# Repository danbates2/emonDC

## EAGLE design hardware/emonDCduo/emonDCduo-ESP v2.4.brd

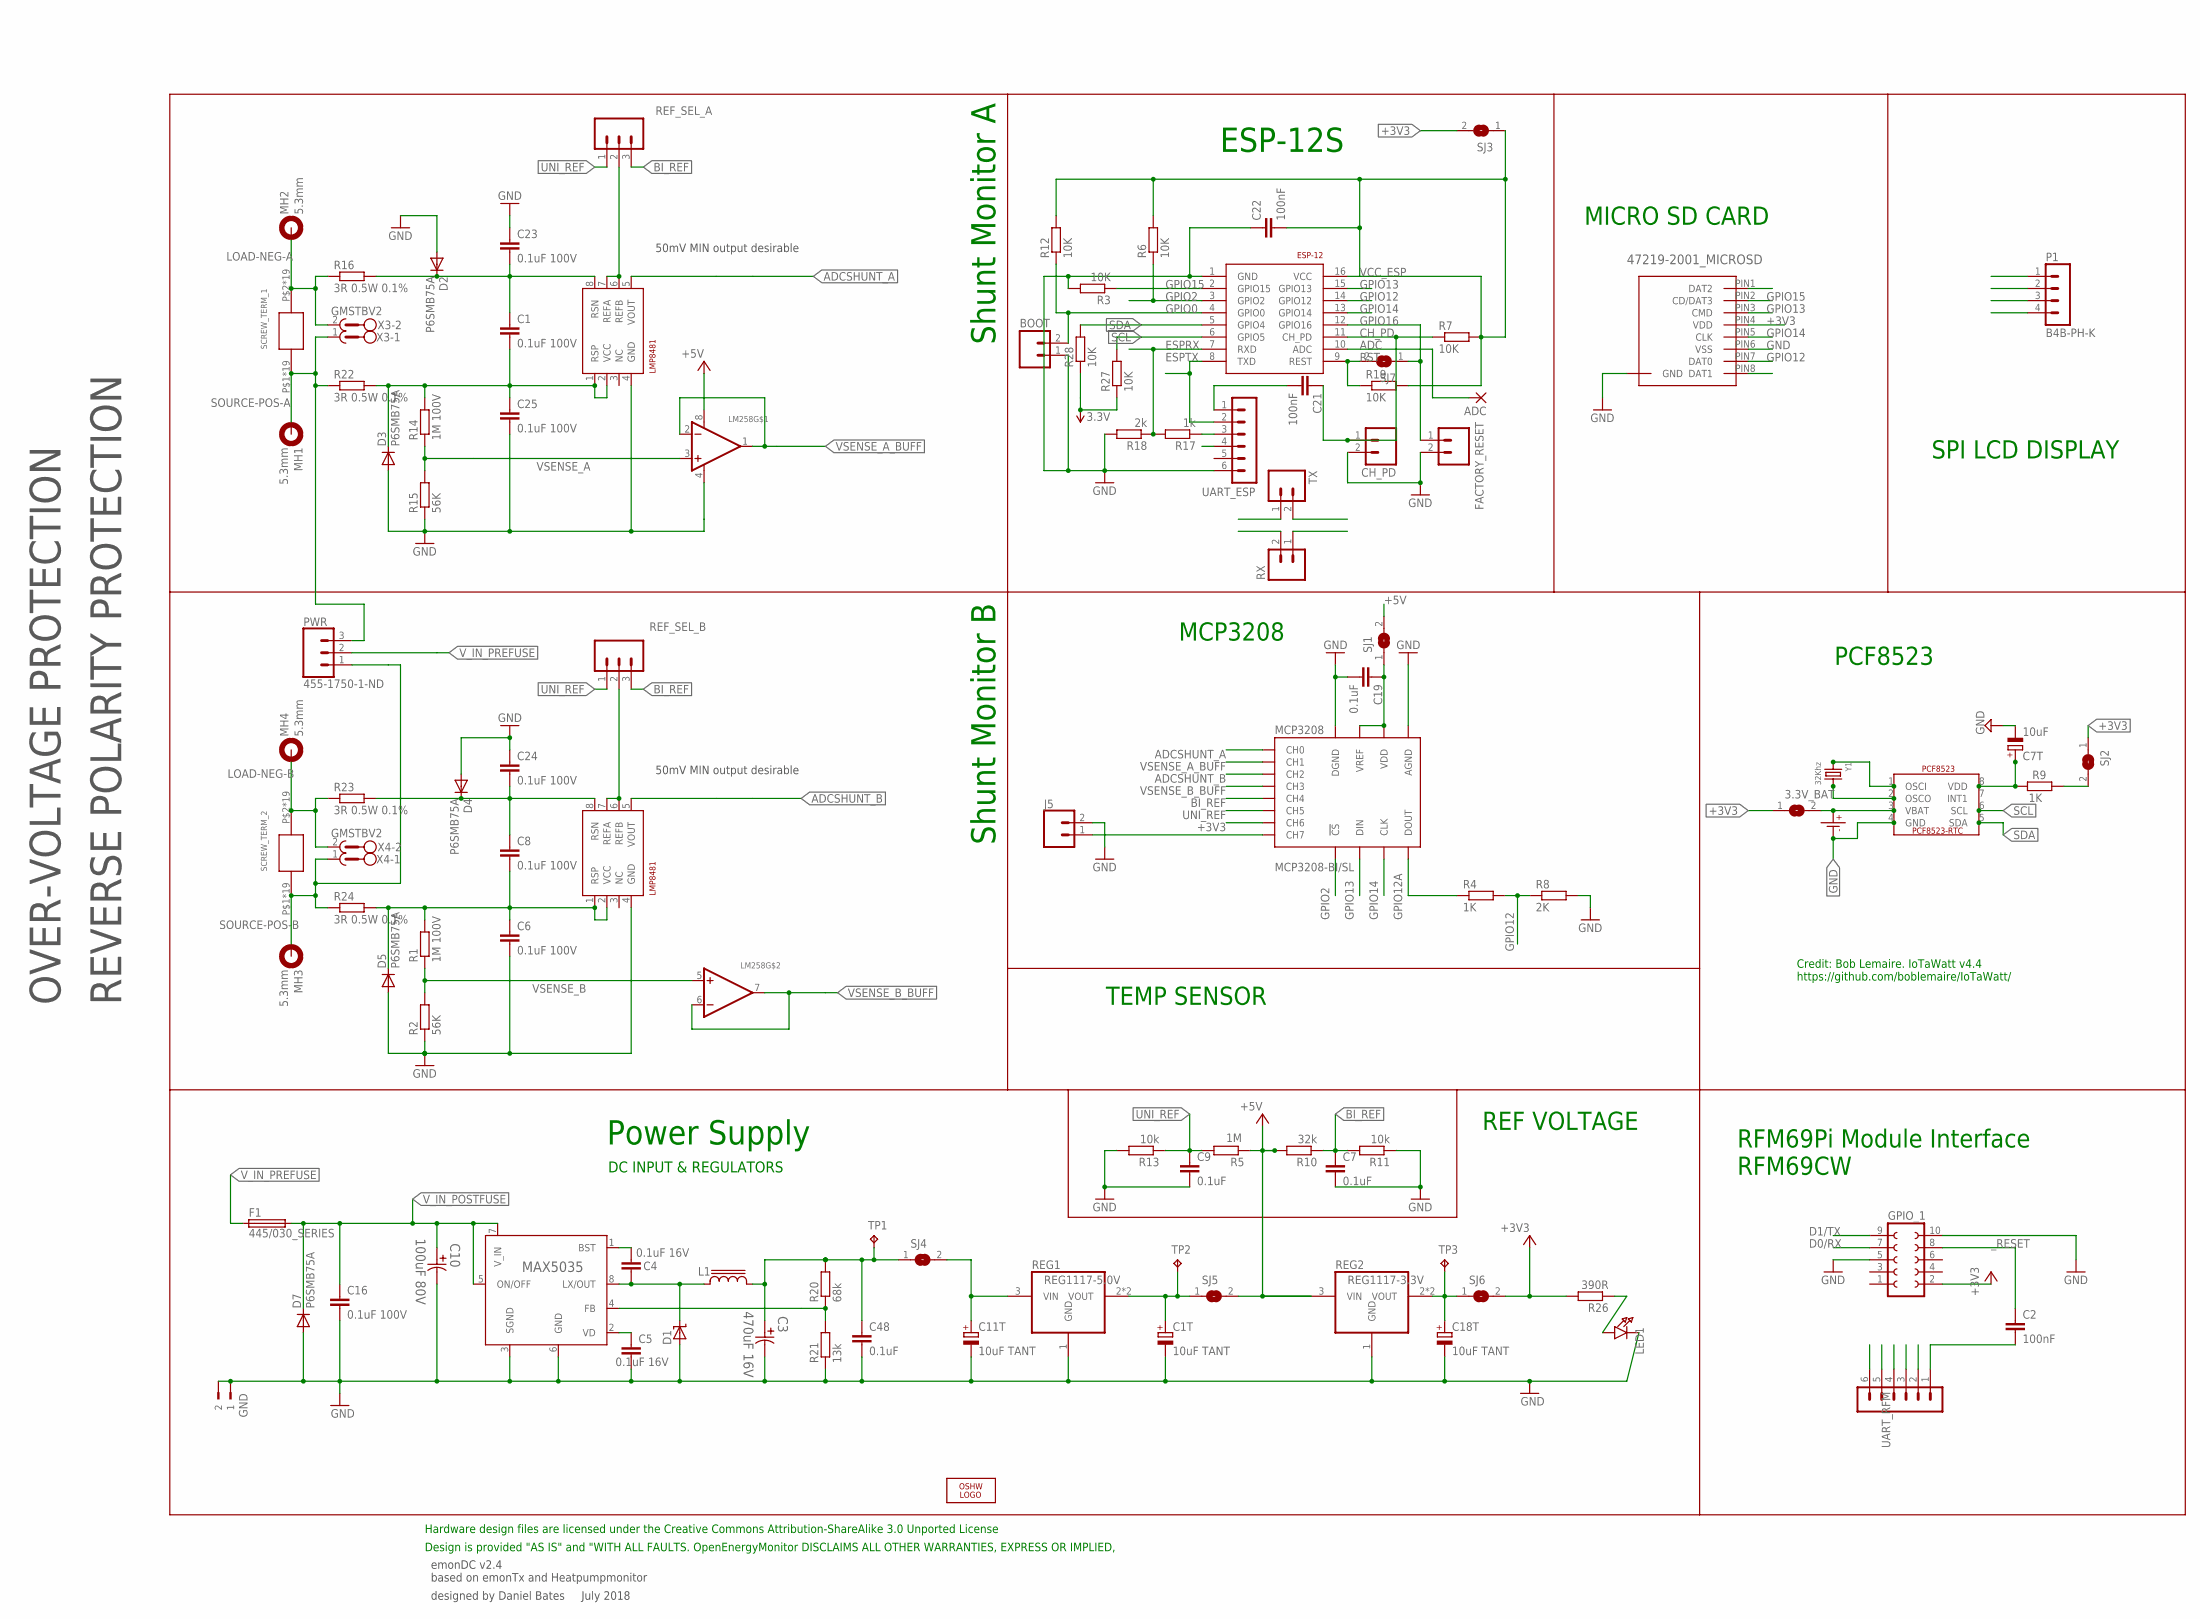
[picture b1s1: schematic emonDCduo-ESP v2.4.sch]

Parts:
3.3V_BAT: SJ-CONCON; SJ-CON
ADC: 2,15/1,0
BOOT: M02PTH; 1X02
C1, C6, C8, C23, C24, C25: 0.1uF 100V; C0603; MPN C1608X7S2A104K080AB
C1T, C11T, C18T: 10uF TANT; C0603POL
C2, C21, C22: 100nF; C0603
C3: 470uF 16V; CAPAE830X1050N
C4, C5: 0.1uF 16V; C0603
C7, C9, C19, C48: 0.1uF; C0603
C7T: 10uF; C0603POL
C10: 100uF 80V; CAPAE1350X1400N
C16: 0.1uF 100V; C0603
CH_PD: M02PTH; 1X02
CR1220: CR1220SMD; MPN Harwin S8411-45R
D1: MBRS1100T3G; SMB_1; MPN MBRS1100T3G
D2, D3, D4, D5, D7: P6SMB75A; DO214AA
ESP-12: ESP8266_ESP-12; ESP8266-ESP12
F1: 445/030_SERIES; 445/030_SERIES_LITTELFUSE
GND: 180-2
GPIO_1: FE05-2_RFM69PI_OUTLINERFM69PI; FE05-2_RFM69PI_OULTINE
IO16: FACTORY_RESET; 1X02
J5: CONN_02; 1X02
L1: SRR1208; SSR1208; MPN SRR1208-151YL
LED1: LED1206; CHIPLED_1206
LM258: LM358; SOIC8_150MIL
LOGO1: OSHW_LOGO_6MILX0200-NT; OSHW_6X200_NOTEXT
MCP3208: MCP3208-BI/SL; SOIC16
MH1, MH2, MH3, MH4: 5.3mm; 5,3//11-PAD
MICRO_SD: 47219-2001_MICROSD
P1: B4B-PH-K
PCF8523: PCF8523_RTC; SOIC_8
PWR: 455-1750-1-ND; 1X03
R1, R14: 1M 100V; R0603; MPN MCWR06X1003FTL
R2, R15: 56K; R0603; MPN MCWR06X5901FTL
R3, R6, R7, R12, R19, R27, R28: 10K; R0603
R4: 1K; R0603; MPN MCWR06X5901FTL
R5: 1M; R0603
R8: 2K; R0603; MPN MCWR06X5901FTL
R9: 1K; R0603
R10: 32k; 0207/10
R11: 10k; 0207/10
R13: 10k; R0603
R16, R22, R23, R24: 3R 0.5W 0.1%; R1206
R17: 1k; R0603
R18: 2k; R0603
R20: 68k; R0603
R21: 13k; R0603
R26: 390R; R0603
REF_SEL_A: 455-1750-1-ND; 1X03; MPN 2212S-02SG-85
REF_SEL_B: 455-1750-1-ND; 1X03; MPN 2212S-02SG-85
REG0: MAX5035; 21-0111D_SBE-14; MPN MAX5035EASA+
REG1: REG1117-5.0V; SOT223; MPN REG1117-5.0
REG2: REG1117-3.3V; SOT223; MPN REG1117-3.3
RX: M02PTH; 1X02
SCREW_TERM_1, SCREW_TERM_2: EBW_SERIES_15.2MM
SHUNTMON-A: LMP8481; S-PDSO-G08; MPN LMP8481MME-S/NOPB
SHUNTMON-B: LMP8481; S-PDSO-G08; MPN LMP8481MME-H/NOPB
SJ1, SJ2, SJ3, SJ4, SJ5, SJ6: SJ-CONCON; SJ-CON
SJ7: SJ
TP1, TP2, TP3: TPPAD1-13; P1-13
TX: M02PTH; 1X02
UART_ESP: UART_ESP; MA06-1
UART_RFM: UART_RFM; MA06-1
X3, X4: GMSTBV2
Y1: 32Khz; CRYSTAL_8X3.8

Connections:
3.3V_PRE: C18T.1 (+), REG2.2 (VOUT), REG2.4 (VOUT), SJ6.1, TP3.TP
5V_PRE: C1T.1 (+), REG1.2 (VOUT), REG1.4 (VOUT), SJ5.1, TP2.TP
6.5V: C11T.1 (+), REG1.3 (VIN), SJ4.2
+3V3: 3.3V_BAT.1, GPIO_1.2, MCP3208.7 (CH6), MICRO_SD.PIN4 (VDD), P1.3, R26.2, R27.1, R28.1, SJ2.1, SJ3.2, SJ6.2
+5V: LM258.8 (V+), R5.1, R10.2, REG2.3 (VIN), SJ1.2, SJ5.2, UART_ESP.4, UART_RFM.4
ADC: ADC.1, ESP-12.10 (ADC)
ADCSHUNT_A: MCP3208.1 (CH0), SHUNTMON-A.5 (VOUT)
ADCSHUNT_B: MCP3208.3 (CH2), SHUNTMON-B.5 (VOUT)
BI_REF: C7.1, MCP3208.5 (CH4), R10.1, R11.2, REF_SEL_A.3, REF_SEL_B.3
BST: C4.1, REG0.1 (BST)
CH7: J5.1, MCP3208.8 (CH7)
CH_PD: C21.1, CH_PD.1, ESP-12.11 (CH_PD), R7.1
D0/RX: GPIO_1.7, TX.2, UART_RFM.2
D1/TX: GPIO_1.9, RX.1, UART_RFM.3
ESPRX: ESP-12.7 (RXD), R17.2, R18.1, RX.2
ESPTX: ESP-12.8 (TXD), TX.1, UART_ESP.2
GND: BOOT.1, C1T.2 (-), C3.2, C5.2, C6.2, C7.2, C7T.2 (-), C9.2, C10.2, C11T.2 (-), C16.2, C18T.2 (-), C19.2, C22.1, C23.1, C24.1, C25.2, C48.2, CH_PD.2, CR1220.P- (P$-), D1.A, D2.A, D3.A, D4.A, D5.A, D7.A, ESP-12.1 (GND), GND.1, GND.2, GPIO_1.5, GPIO_1.10, IO16.2, J5.2, LED1.C, LM258.4 (V-), MCP3208.9 (DGND), MCP3208.14 (AGND), MICRO_SD.P$1 (GND), MICRO_SD.P$2 (GND), MICRO_SD.P$3 (GND), MICRO_SD.P$4 (GND), MICRO_SD.PIN6 (VSS), P1.4, PCF8523.4 (GND), R2.1, R3.2, R8.2, R11.1, R13.2, R15.1, R18.2, R21.1, REG0.3 (SGND), REG0.6 (GND), REG1.1 (GND), REG2.1 (GND), SHUNTMON-A.4 (GND), SHUNTMON-B.4 (GND), UART_ESP.6, UART_RFM.6
GPIO0: BOOT.2, ESP-12.4 (GPIO0), R12.1
GPIO2: ESP-12.3 (GPIO2), MCP3208.10 (!CS), R6.1
GPIO12: ESP-12.14 (GPIO12), MICRO_SD.PIN7 (DAT0), R4.2, R8.1
GPIO12A: MCP3208.12 (DOUT), R4.1
GPIO13: ESP-12.15 (GPIO13), MCP3208.11 (DIN), MICRO_SD.PIN3 (CMD)
GPIO14: ESP-12.13 (GPIO14), MCP3208.13 (CLK), MICRO_SD.PIN5 (CLK)
GPIO15: ESP-12.2 (GPIO15), MICRO_SD.PIN2 (CD/DAT3), R3.1
GPIO16: ESP-12.12 (GPIO16), IO16.1, SJ7.1
LOAD-NEG-A: MH2.B5,5, R16.1, SCREW_TERM_1.P$2, SCREW_TERM_1.P$18, SCREW_TERM_1.P$19, SCREW_TERM_1.P$20, SCREW_TERM_1.P$21, SCREW_TERM_1.P$22, SCREW_TERM_1.P$23, SCREW_TERM_1.P$24, SCREW_TERM_1.P$25, SCREW_TERM_1.P$26, SCREW_TERM_1.P$27, SCREW_TERM_1.P$28, SCREW_TERM_1.P$29, SCREW_TERM_1.P$30, SCREW_TERM_1.P$31, SCREW_TERM_1.P$32, SCREW_TERM_1.P$36, SCREW_TERM_1.P$37, SCREW_TERM_1.P$38, X3.2
LOAD-NEG-A_T: C1.1, C23.2, D2.C, R16.2, SHUNTMON-A.8 (RSN)
LOAD-NEG-B: MH4.B5,5, R23.1, SCREW_TERM_2.P$2, SCREW_TERM_2.P$18, SCREW_TERM_2.P$19, SCREW_TERM_2.P$20, SCREW_TERM_2.P$21, SCREW_TERM_2.P$22, SCREW_TERM_2.P$23, SCREW_TERM_2.P$24, SCREW_TERM_2.P$25, SCREW_TERM_2.P$26, SCREW_TERM_2.P$27, SCREW_TERM_2.P$28, SCREW_TERM_2.P$29, SCREW_TERM_2.P$30, SCREW_TERM_2.P$31, SCREW_TERM_2.P$32, SCREW_TERM_2.P$36, SCREW_TERM_2.P$37, SCREW_TERM_2.P$38, X4.2
LOAD-NEG-B_T: C8.1, C24.2, D4.C, R23.2, SHUNTMON-B.8 (RSN)
LX: C4.2, D1.C, L1.1, REG0.8 (LX/OUT)
MCP_VCC: C19.1, MCP3208.15 (VREF), MCP3208.16 (VDD), SJ1.1
unnamed: R20.1, R21.2, REG0.4 (FB)
unnamed: LED1.A, R26.1
unnamed: C7T.1 (+), PCF8523.8 (VDD), R9.1
unnamed: R9.2, SJ2.2
unnamed: C21.2, UART_ESP.1
unnamed: R17.1, UART_ESP.3
unnamed: PCF8523.2 (OSCO), Y1.P$4 (2)
unnamed: PCF8523.1 (OSCI), Y1.P$1 (1)
unnamed: C2.2, UART_RFM.1
PRE_6.5V: C3.1, C48.1, L1.2, R20.2, SJ4.1, TP1.TP
REF_A_INPUT: REF_SEL_A.2, SHUNTMON-A.6 (REFB), SHUNTMON-A.7 (REFA)
REF_B_INPUT: REF_SEL_B.2, SHUNTMON-B.6 (REFB), SHUNTMON-B.7 (REFA)
RST: ESP-12.9 (REST), R19.1, SJ7.2
SCL: ESP-12.6 (GPIO5), P1.2, PCF8523.6 (SCL), R27.2
SDA: ESP-12.5 (GPIO4), P1.1, PCF8523.5 (SDA), R28.2
SOURCE-POS-A: MH1.B5,5, PWR.3, R22.1, SCREW_TERM_1.P$1, SCREW_TERM_1.P$3, SCREW_TERM_1.P$4, SCREW_TERM_1.P$5, SCREW_TERM_1.P$6, SCREW_TERM_1.P$7, SCREW_TERM_1.P$8, SCREW_TERM_1.P$9, SCREW_TERM_1.P$10, SCREW_TERM_1.P$11, SCREW_TERM_1.P$12, SCREW_TERM_1.P$13, SCREW_TERM_1.P$14, SCREW_TERM_1.P$15, SCREW_TERM_1.P$16, SCREW_TERM_1.P$17, SCREW_TERM_1.P$33, SCREW_TERM_1.P$34, SCREW_TERM_1.P$35, X3.1
SOURCE-POS-A_T: C1.2, C25.1, D3.C, R14.2, R22.2, SHUNTMON-A.1 (RSP), SHUNTMON-A.2 (VCC)
SOURCE-POS-B: MH3.B5,5, PWR.1, R24.1, SCREW_TERM_2.P$1, SCREW_TERM_2.P$3, SCREW_TERM_2.P$4, SCREW_TERM_2.P$5, SCREW_TERM_2.P$6, SCREW_TERM_2.P$7, SCREW_TERM_2.P$8, SCREW_TERM_2.P$9, SCREW_TERM_2.P$10, SCREW_TERM_2.P$11, SCREW_TERM_2.P$12, SCREW_TERM_2.P$13, SCREW_TERM_2.P$14, SCREW_TERM_2.P$15, SCREW_TERM_2.P$16, SCREW_TERM_2.P$17, SCREW_TERM_2.P$33, SCREW_TERM_2.P$34, SCREW_TERM_2.P$35, X4.1
SOURCE-POS-B_T: C6.1, C8.2, D5.C, R1.2, R24.2, SHUNTMON-B.1 (RSP), SHUNTMON-B.2 (VCC)
UNI_REF: C9.1, MCP3208.6 (CH5), R5.2, R13.1, REF_SEL_A.1, REF_SEL_B.1
VBAT: 3.3V_BAT.2, CR1220.P+ (P$+), PCF8523.3 (VBAT)
VCC_ESP: C22.2, ESP-12.16 (VCC), R6.2, R7.2, R12.2, R19.2, SJ3.1
VD: C5.1, REG0.2 (VD)
VSENSE_A: LM258.3 (+IN), R14.1, R15.2
VSENSE_A_BUFF: LM258.1 (OUT), LM258.2 (-IN), MCP3208.2 (CH1)
VSENSE_B: LM258.5 (+IN), R1.1, R2.2
VSENSE_B_BUFF: LM258.6 (-IN), LM258.7 (OUT), MCP3208.4 (CH3)
V_IN_POSTFUSE: C10.1, C16.1, D7.C, F1.P$3 (2), F1.P$4 (2), REG0.5 (ON/OFF), REG0.7 (V_IN)
V_IN_PREFUSE: F1.P$1 (1), F1.P$2 (1), PWR.2
_RESET: C2.1, GPIO_1.8

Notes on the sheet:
emonDC v2.4 based on emonTx and Heatpumpmonitor
designed by Daniel Bates July 2018
Power Supply
Design is provided "AS IS" and "WITH ALL FAULTS. OpenEnergyMonitor DISCLAIMS ALL OTHER WARRANTIES, EXPRESS OR IMPLIED,
Hardware design files are licensed under the Creative Commons Attribution-ShareAlike 3.0 Unported License
DC INPUT & REGULATORS
Shunt Monitor B
Shunt Monitor A
ESP-12S
MICRO SD CARD
RFM69Pi Module Interface RFM69CW
MCP3208
PCF8523
Credit: Bob Lemaire. IoTaWatt v4.4 https://github.com/boblemaire/IoTaWatt/
SPI LCD DISPLAY
TEMP SENSOR
50mV MIN output desirable
REVERSE POLARITY PROTECTION
OVER-VOLTAGE PROTECTION
REF VOLTAGE

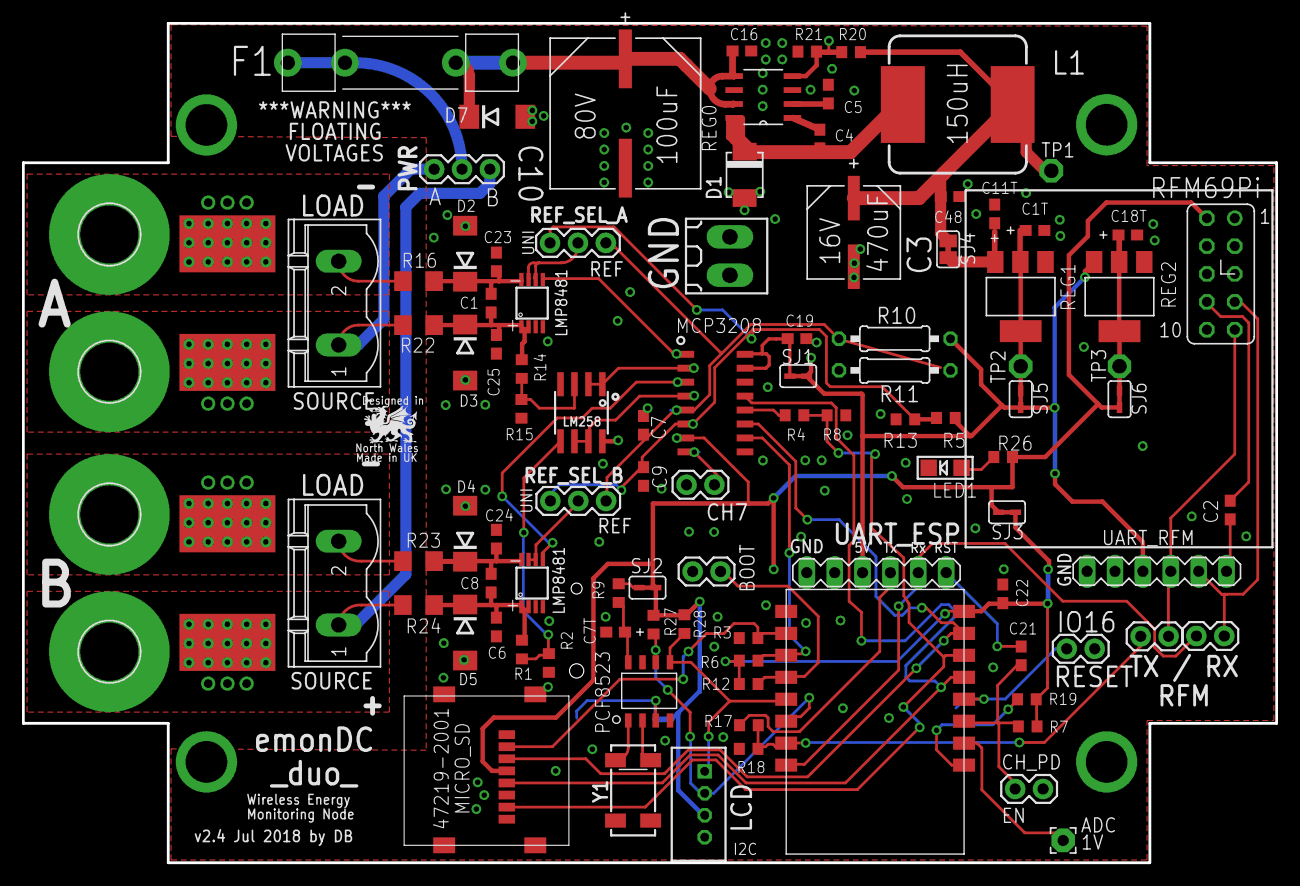
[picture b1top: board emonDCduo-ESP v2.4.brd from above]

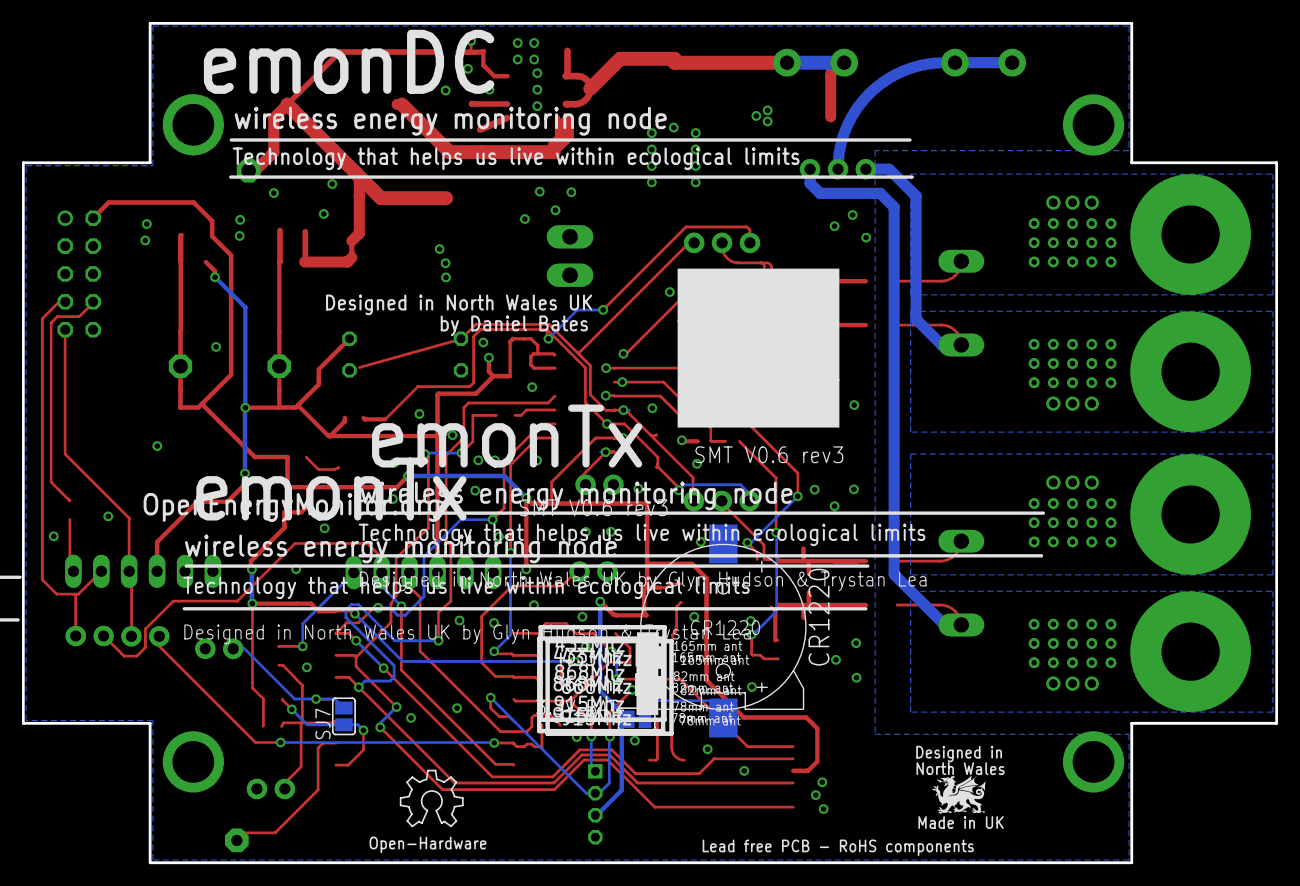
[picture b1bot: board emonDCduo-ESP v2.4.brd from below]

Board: 2 copper layers, 114.2 x 76.5 mm, 108 parts (5 on the bottom side), 61 nets.

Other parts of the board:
U$1: DRAGON_LOGO_NOTEXT
U$2, U$3: ALIGNMENT_STOP

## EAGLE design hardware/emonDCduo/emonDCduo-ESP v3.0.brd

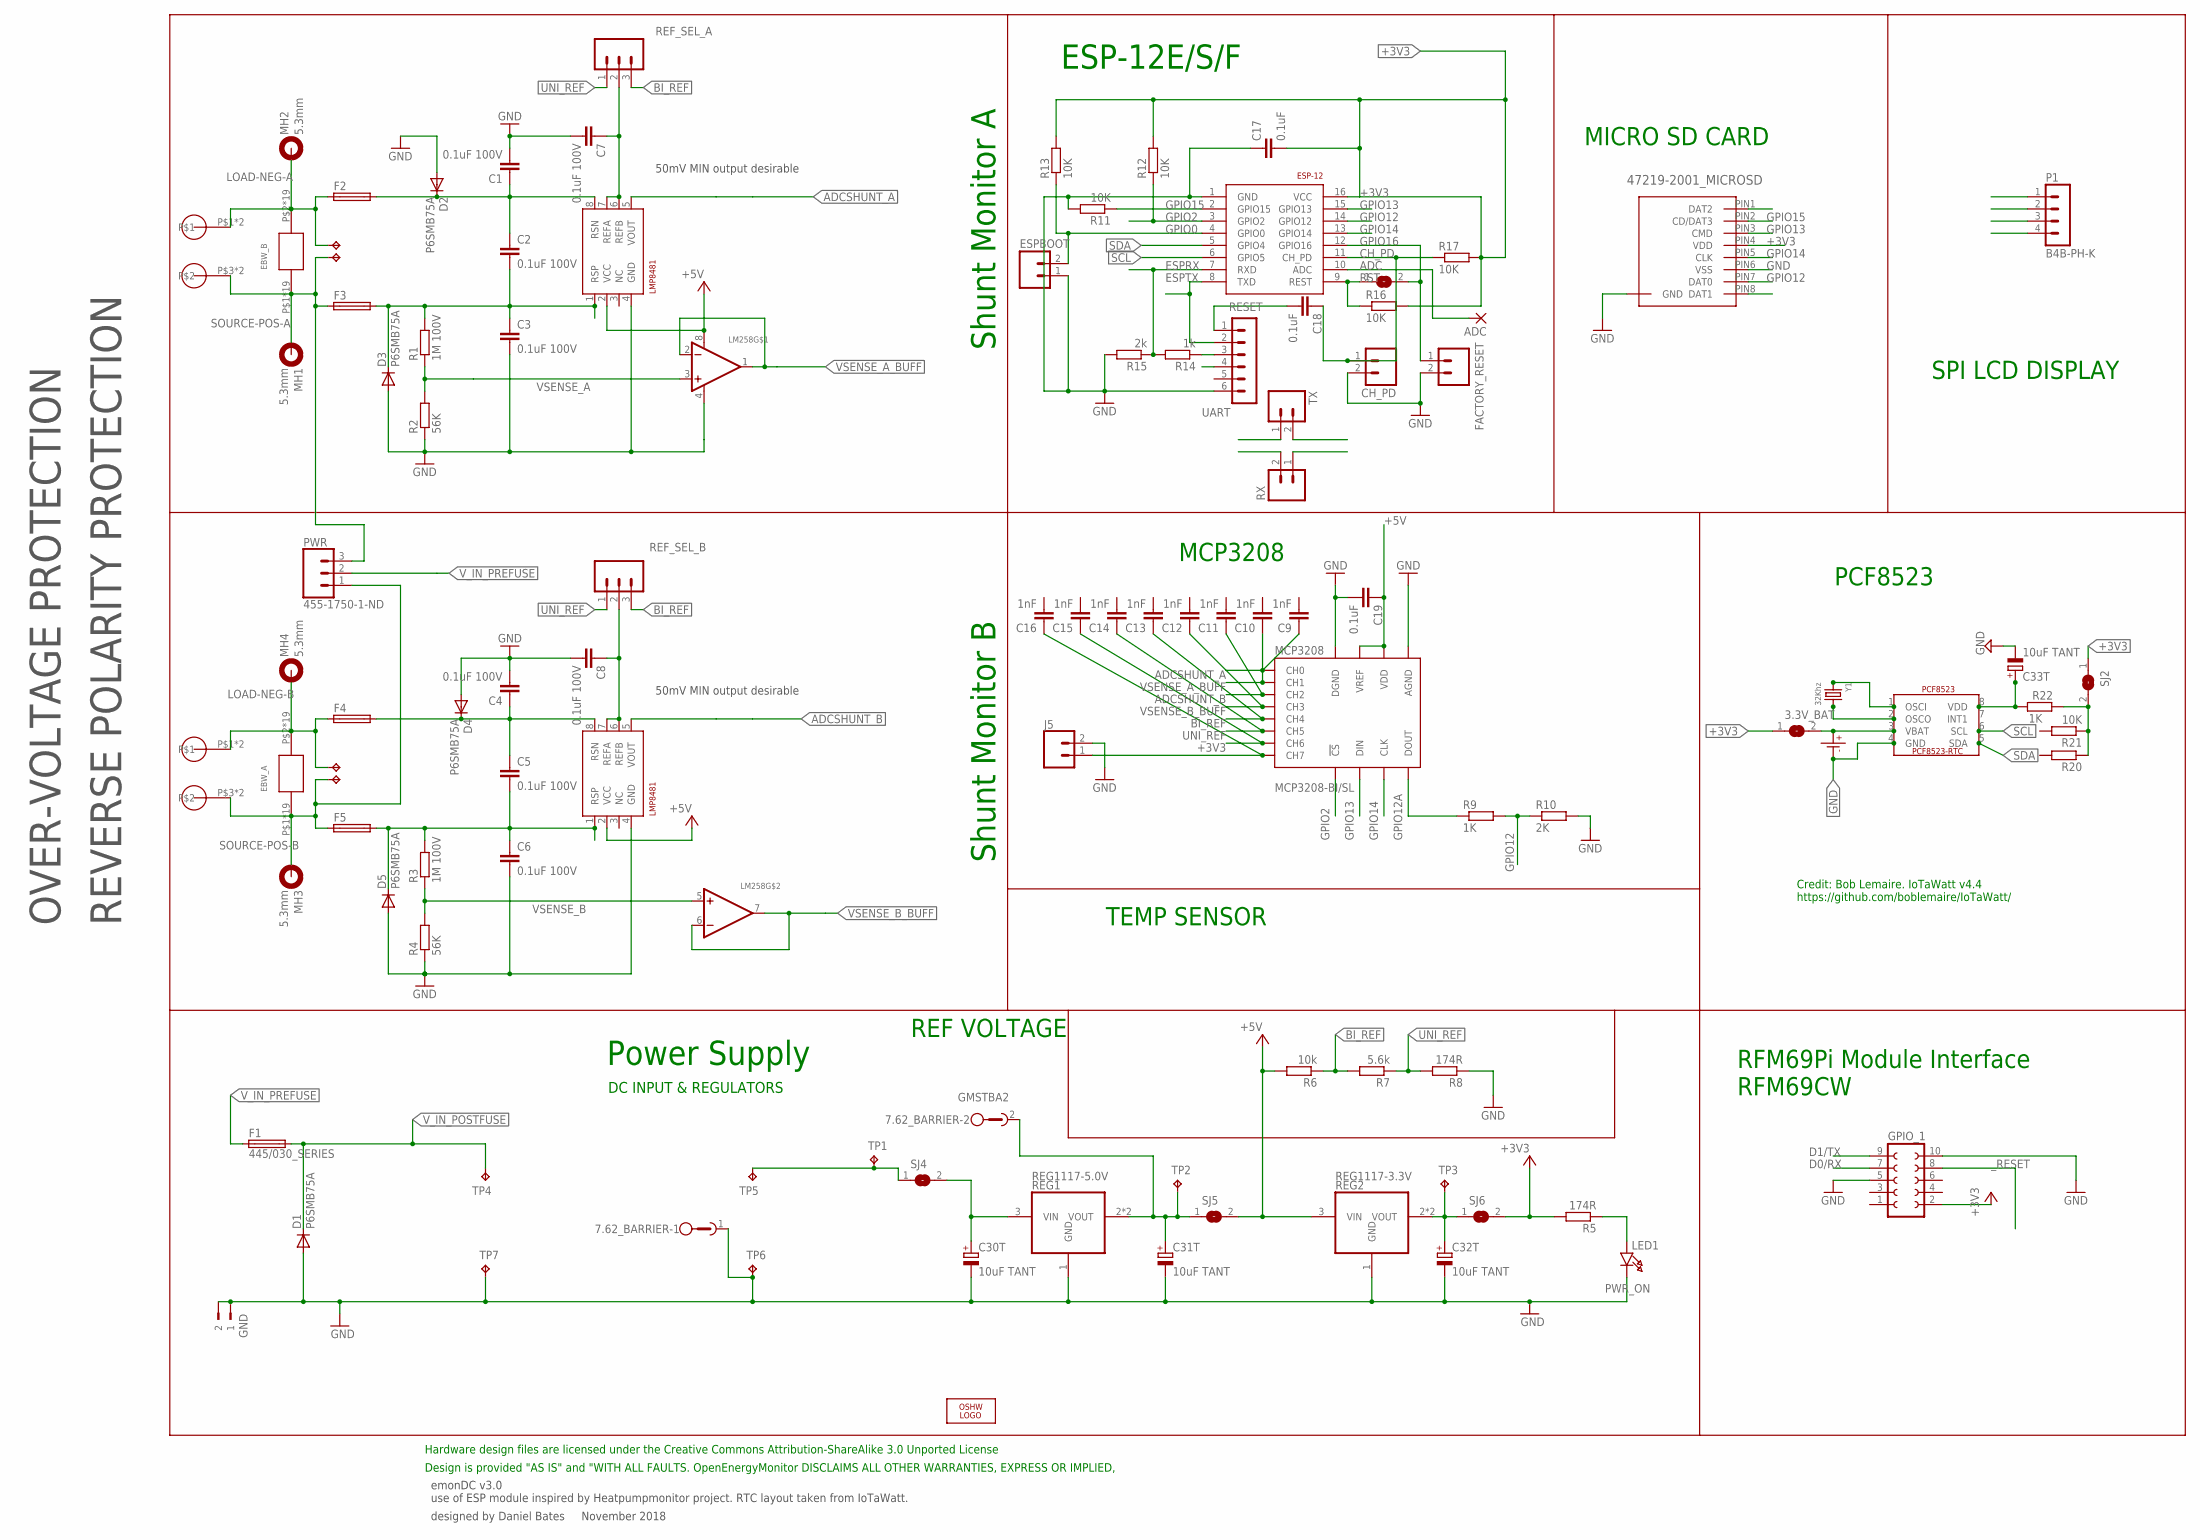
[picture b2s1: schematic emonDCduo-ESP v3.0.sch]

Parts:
3.3V_BAT: SJ-CONCON; SJ-CON
7.62_BARRIER: GMSTBA2
ADC: 2,15/1,0
C1, C2, C3, C4, C5, C6, C7, C8: 0.1uF 100V; C0603; MPN C1608X7S2A104K080AB
C9, C10, C11, C12, C13, C14, C15, C16: 1nF; C0603
C17, C18, C19: 0.1uF; C0603
C30T, C31T, C32T, C33T: 10uF TANT; C0603POL
CH_PD: M02PTH; 1X02
CR1220: CR1220SMD; MPN Harwin S8411-45R
D1, D2, D3, D4, D5: P6SMB75A; DO214AA
EBW_A: EBW_SERIES_15.2MM
EBW_B: EBW_SERIES_15.2MM
ESP-12: ESP8266_ESP-12; ESP8266-ESP12
ESPBOOT: M02PTH; 1X02
F1: 445/030_SERIES; 445/030_SERIES_LITTELFUSE
F2, F3, F4, F5: TR5
GND: 180-2
GPIO_1: FE05-2_RFM69PI_OUTLINERFM69PI; FE05-2_RFM69PI_OULTINE
IO16: FACTORY_RESET; 1X02
J5: CONN_02; 1X02
LED1: PWR_ON; CHIPLED_1206
LM258: LM358; SOIC8_150MIL
LOGO1: OSHW_LOGO_6MILX0200-NT; OSHW_6X200_NOTEXT
MCP3208: MCP3208-BI/SL; SOIC16
MH1, MH2, MH3, MH4: 5.3mm; 5,3//11-PAD
MICRO_SD: 47219-2001_MICROSD
MOUNT_10.16_A, MOUNT_10.16_B: MOLEX_39970-003; 2/10,16
P1: B4B-PH-K
PCF8523: PCF8523_RTC; SOIC_8
PWR: 455-1750-1-ND; 1X03
R1, R3: 1M 100V; R0603; MPN MCWR06X1003FTL
R2, R4: 56K; R0603; MPN MCWR06X5901FTL
R5: 174R; R0603
R6: 10k; 0207/10
R7: 5.6k; 0207/10
R8: 174R; 0207/10
R9: 1K; R0603; MPN MCWR06X5901FTL
R10: 2K; R0603; MPN MCWR06X5901FTL
R11, R12, R13, R16, R17, R20, R21: 10K; R0603
R14: 1k; R0603
R15: 2k; R0603
R22: 1K; R0603
REF_SEL_A: 455-1750-1-ND; 1X03; MPN 2212S-02SG-85
REF_SEL_B: 455-1750-1-ND; 1X03; MPN 2212S-02SG-85
REG1: REG1117-5.0V; SOT223; MPN REG1117-5.0
REG2: REG1117-3.3V; SOT223; MPN REG1117-3.3
RX: M02PTH; 1X02
SHUNTMON-A: LMP8481; S-PDSO-G08; MPN LMP8481MME-S/NOPB
SHUNTMON-B: LMP8481; S-PDSO-G08; MPN LMP8481MME-H/NOPB
SJ1, SJ4, SJ5, SJ6: SJ-CONCON; SJ-CON
SJ2: SJ
TP1, TP2, TP3: TPPAD1-13; P1-13
TP4, TP5, TP6, TP7, TP8, TP9, TP10, TP11: TPPAD1-13Y; P1-13Y
TX: M02PTH; 1X02
UART: UART; MA06-1
Y1: 32Khz; CRYSTAL_8X3.8

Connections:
3.3V_PRE: C32T.1 (+), REG2.2 (VOUT), REG2.4 (VOUT), SJ6.1, TP3.TP
5V_PRE: 7.62_BARRIER.2, C31T.1 (+), REG1.2 (VOUT), REG1.4 (VOUT), SJ5.1, TP2.TP
6.5V: C30T.1 (+), REG1.3 (VIN), SJ4.2
+3V3: 3.3V_BAT.1, C15.1, C17.2, ESP-12.16 (VCC), GPIO_1.2, MCP3208.7 (CH6), MICRO_SD.PIN4 (VDD), P1.3, R5.2, R12.2, R13.2, R16.2, R17.2, SJ2.1, SJ6.2
+5V: C19.1, LM258.8 (V+), MCP3208.15 (VREF), MCP3208.16 (VDD), R6.2, REG2.3 (VIN), SHUNTMON-A.2 (VCC), SHUNTMON-B.2 (VCC), SJ5.2, UART.4
ADC: ADC.1, ESP-12.10 (ADC)
ADCSHUNT_A: C9.1, MCP3208.1 (CH0), SHUNTMON-A.5 (VOUT)
ADCSHUNT_B: C11.1, MCP3208.3 (CH2), SHUNTMON-B.5 (VOUT)
BI_REF: C13.1, MCP3208.5 (CH4), R6.1, R7.2, REF_SEL_A.3, REF_SEL_B.3
CH7: C16.1, J5.1, MCP3208.8 (CH7)
CH_PD: C18.1, CH_PD.1, ESP-12.11 (CH_PD), R17.1
D0/RX: GPIO_1.7, TX.2
D1/TX: GPIO_1.9, RX.1
ESPRX: ESP-12.7 (RXD), R14.2, R15.1, RX.2
ESPTX: ESP-12.8 (TXD), TX.1, UART.2
GND: 7.62_BARRIER.1, C1.2, C3.2, C4.2, C6.2, C7.2, C8.2, C17.1, C19.2, C30T.2 (-), C31T.2 (-), C32T.2 (-), C33T.2 (-), CH_PD.2, CR1220.P- (P$-), D1.A, D2.A, D3.A, D4.A, D5.A, ESP-12.1 (GND), ESPBOOT.1, GND.1, GND.2, GPIO_1.5, GPIO_1.10, IO16.2, J5.2, LED1.C, LM258.4 (V-), MCP3208.9 (DGND), MCP3208.14 (AGND), MICRO_SD.P$1 (GND), MICRO_SD.P$2 (GND), MICRO_SD.P$3 (GND), MICRO_SD.P$4 (GND), MICRO_SD.PIN6 (VSS), P1.4, PCF8523.4 (GND), R2.1, R4.1, R8.1, R10.2, R11.2, R15.2, REG1.1 (GND), REG2.1 (GND), SHUNTMON-A.4 (GND), SHUNTMON-B.4 (GND), TP6.TP, TP7.TP, UART.6
GPIO0: ESP-12.4 (GPIO0), ESPBOOT.2, R13.1
GPIO2: ESP-12.3 (GPIO2), MCP3208.10 (!CS), R12.1
GPIO12: ESP-12.14 (GPIO12), MICRO_SD.PIN7 (DAT0), R9.2, R10.1
GPIO12A: MCP3208.12 (DOUT), R9.1
GPIO13: ESP-12.15 (GPIO13), MCP3208.11 (DIN), MICRO_SD.PIN3 (CMD)
GPIO14: ESP-12.13 (GPIO14), MCP3208.13 (CLK), MICRO_SD.PIN5 (CLK)
GPIO15: ESP-12.2 (GPIO15), MICRO_SD.PIN2 (CD/DAT3), R11.1
GPIO16: ESP-12.12 (GPIO16), IO16.1, SJ1.2
LOAD-NEG-A: EBW_B.P$2, EBW_B.P$18, EBW_B.P$19, EBW_B.P$20, EBW_B.P$21, EBW_B.P$22, EBW_B.P$23, EBW_B.P$24, EBW_B.P$25, EBW_B.P$26, EBW_B.P$27, EBW_B.P$28, EBW_B.P$29, EBW_B.P$30, EBW_B.P$31, EBW_B.P$32, EBW_B.P$36, EBW_B.P$37, EBW_B.P$38, F2.1, MH2.B5,5, MOUNT_10.16_A.P$1, MOUNT_10.16_A.P$2, TP11.TP
LOAD-NEG-A_T: C1.1, C2.1, D2.C, F2.2, SHUNTMON-A.8 (RSN)
LOAD-NEG-B: EBW_A.P$2, EBW_A.P$18, EBW_A.P$19, EBW_A.P$20, EBW_A.P$21, EBW_A.P$22, EBW_A.P$23, EBW_A.P$24, EBW_A.P$25, EBW_A.P$26, EBW_A.P$27, EBW_A.P$28, EBW_A.P$29, EBW_A.P$30, EBW_A.P$31, EBW_A.P$32, EBW_A.P$36, EBW_A.P$37, EBW_A.P$38, F4.1, MH4.B5,5, MOUNT_10.16_B.P$1, MOUNT_10.16_B.P$2, TP9.TP
LOAD-NEG-B_T: C4.1, C5.1, D4.C, F4.2, SHUNTMON-B.8 (RSN)
unnamed: SJ4.1, TP1.TP, TP5.TP
unnamed: LED1.A, R5.1
unnamed: R14.1, UART.3
unnamed: PCF8523.2 (OSCO), Y1.P$4 (2)
unnamed: PCF8523.1 (OSCI), Y1.P$1 (1)
REF_A_INPUT: C7.1, REF_SEL_A.2, SHUNTMON-A.6 (REFB), SHUNTMON-A.7 (REFA)
REF_B_INPUT: C8.1, REF_SEL_B.2, SHUNTMON-B.6 (REFB), SHUNTMON-B.7 (REFA)
RESET: C18.2, UART.1
RST: ESP-12.9 (REST), R16.1, SJ1.1
SCL: ESP-12.6 (GPIO5), P1.2, PCF8523.6 (SCL)
SDA: ESP-12.5 (GPIO4), P1.1, PCF8523.5 (SDA)
SOURCE-POS-A: EBW_B.P$1, EBW_B.P$3, EBW_B.P$4, EBW_B.P$5, EBW_B.P$6, EBW_B.P$7, EBW_B.P$8, EBW_B.P$9, EBW_B.P$10, EBW_B.P$11, EBW_B.P$12, EBW_B.P$13, EBW_B.P$14, EBW_B.P$15, EBW_B.P$16, EBW_B.P$17, EBW_B.P$33, EBW_B.P$34, EBW_B.P$35, F3.1, MH1.B5,5, MOUNT_10.16_A.P$3, MOUNT_10.16_A.P$4, PWR.3, TP10.TP
SOURCE-POS-A_T: C2.2, C3.1, D3.C, F3.2, R1.2, SHUNTMON-A.1 (RSP)
SOURCE-POS-B: EBW_A.P$1, EBW_A.P$3, EBW_A.P$4, EBW_A.P$5, EBW_A.P$6, EBW_A.P$7, EBW_A.P$8, EBW_A.P$9, EBW_A.P$10, EBW_A.P$11, EBW_A.P$12, EBW_A.P$13, EBW_A.P$14, EBW_A.P$15, EBW_A.P$16, EBW_A.P$17, EBW_A.P$33, EBW_A.P$34, EBW_A.P$35, F5.1, MH3.B5,5, MOUNT_10.16_B.P$3, MOUNT_10.16_B.P$4, PWR.1, TP8.TP
SOURCE-POS-B_T: C5.2, C6.1, D5.C, F5.2, R3.2, SHUNTMON-B.1 (RSP)
UNI_REF: C14.1, MCP3208.6 (CH5), R7.1, R8.2, REF_SEL_A.1, REF_SEL_B.1
VBAT: 3.3V_BAT.2, CR1220.P+ (P$+), PCF8523.3 (VBAT)
VDD_PCF: C33T.1 (+), PCF8523.8 (VDD), R22.1
VDD_RTC_POSTJUMPER: R20.1, R21.1, R22.2, SJ2.2
VSENSE_A: LM258.3 (+IN), R1.1, R2.2
VSENSE_A_BUFF: C10.1, LM258.1 (OUT), LM258.2 (-IN), MCP3208.2 (CH1)
VSENSE_B: LM258.5 (+IN), R3.1, R4.2
VSENSE_B_BUFF: C12.1, LM258.6 (-IN), LM258.7 (OUT), MCP3208.4 (CH3)
V_IN_POSTFUSE: D1.C, F1.P$3 (2), F1.P$4 (2), TP4.TP
V_IN_PREFUSE: F1.P$1 (1), F1.P$2 (1), PWR.2
_RESET: GPIO_1.8

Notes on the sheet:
emonDC v3.0 use of ESP module inspired by Heatpumpmonitor project. RTC layout taken from IoTaWatt.
designed by Daniel Bates November 2018
Power Supply
Design is provided "AS IS" and "WITH ALL FAULTS. OpenEnergyMonitor DISCLAIMS ALL OTHER WARRANTIES, EXPRESS OR IMPLIED,
Hardware design files are licensed under the Creative Commons Attribution-ShareAlike 3.0 Unported License
DC INPUT & REGULATORS
Shunt Monitor B
Shunt Monitor A
ESP-12E/S/F
MICRO SD CARD
RFM69Pi Module Interface RFM69CW
MCP3208
PCF8523
Credit: Bob Lemaire. IoTaWatt v4.4 https://github.com/boblemaire/IoTaWatt/
SPI LCD DISPLAY
TEMP SENSOR
50mV MIN output desirable
REVERSE POLARITY PROTECTION
OVER-VOLTAGE PROTECTION
REF VOLTAGE

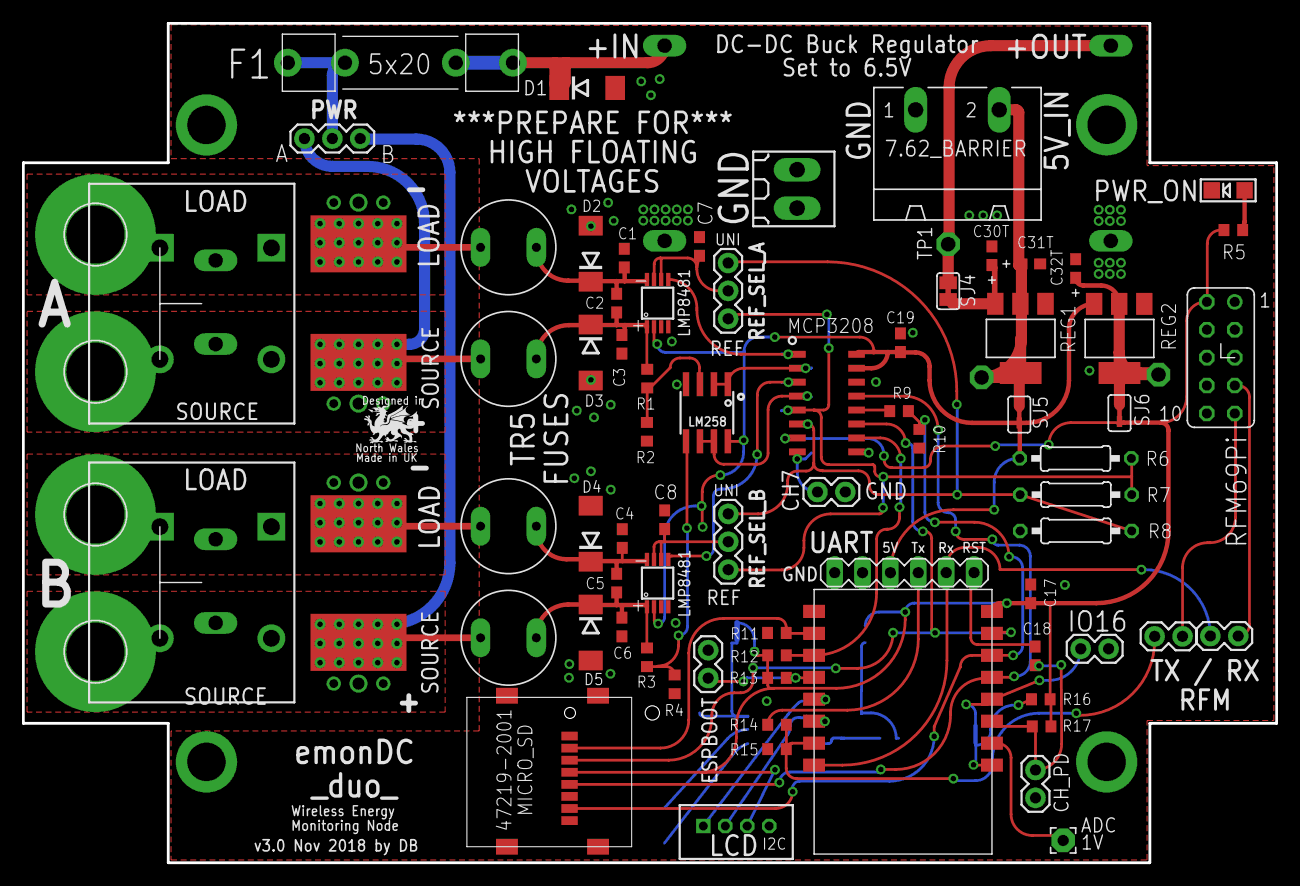
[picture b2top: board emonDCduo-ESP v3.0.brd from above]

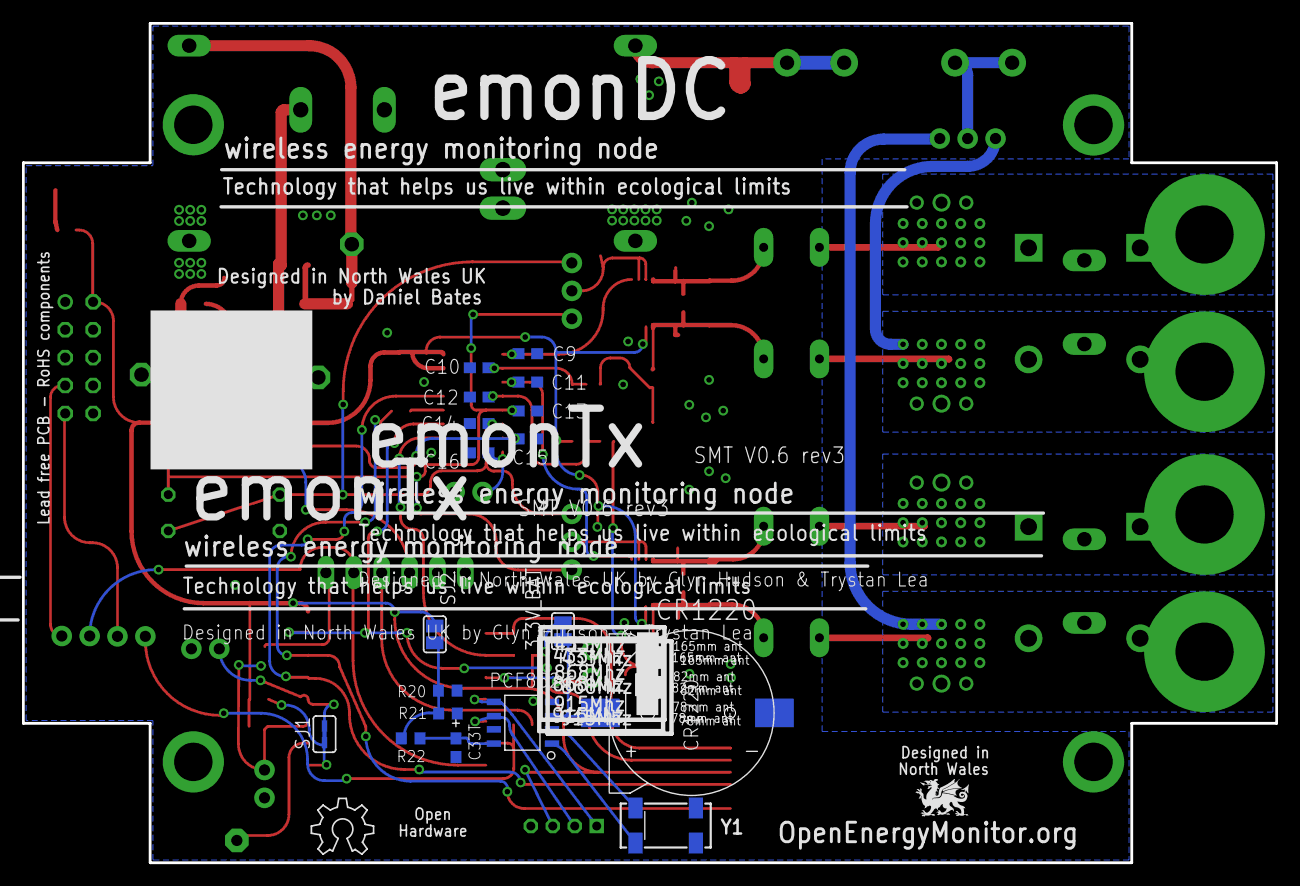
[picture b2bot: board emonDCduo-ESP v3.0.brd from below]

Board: 2 copper layers, 114.2 x 76.5 mm, 109 parts (20 on the bottom side), 53 nets.

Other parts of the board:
U$1: DRAGON_LOGO_NOTEXT
U$2, U$3: ALIGNMENT_STOP

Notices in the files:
parts and their libraries:
SparkFun-Connectors: Licensing: CC v3.0 Share-Alike You are welcome to use this library for commercial purposes.
microbuilder: This work is placed in the public domain, and may be freely used for commercial and non-commercial work with the following conditions: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
JST-PH: Copyright (C) 2016, Bob Starr
